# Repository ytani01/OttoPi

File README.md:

# OttoPi: Otto DIY like biped robot for Raspberry Pi

see [github pages](https://ytani01.github.io/OttoPi/)

## Power ON/OFF Button

### Power ON button

GPIO 3 -> SW -> GND

### Shutdown button

GPIO 4 -> SW -> GND
GPIO 21 -> R(1K ohm) -> LED -> GND

```
dtoverlay=gpio-shutdown,gpio_pin=4
dtoverlay=gpio-poweroff,gpiopin=21,active_low=1
```

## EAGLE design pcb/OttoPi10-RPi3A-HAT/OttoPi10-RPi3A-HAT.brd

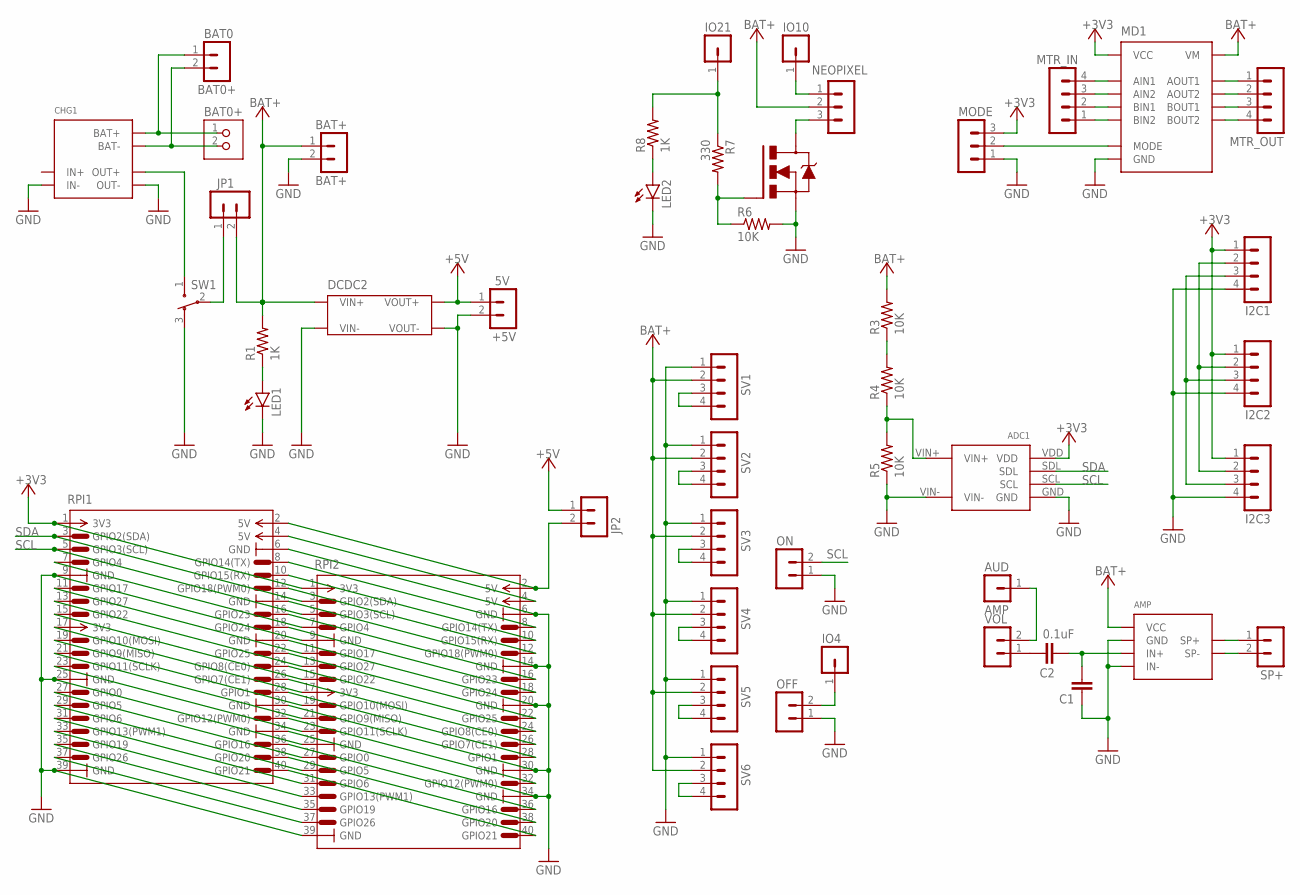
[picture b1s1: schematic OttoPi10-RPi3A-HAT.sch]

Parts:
+5V: 5V; PINHEAD-MA02-1
ADC1: MCP3425MOD
AMP: AMP; PAM8012MOD-A
AUD: AMP; PINHEAD-MA01-1
BAT0: BAT0+; PINHEAD-MA02-1
BAT0+: JST-PH2
BAT+: BAT+; PINHEAD-MA02-1
C1: C-EU025-024X044; C025-024X044
C2: 0.1uF; C025-024X044
CHG1: TP4056MOD1
DCDC2: DCDC-SX1308-MOD1
I2C1, I2C2, I2C3: PINHEAD-MA04-1
IO4, IO10, IO21: PINHEAD-MA01-1
JP1, JP2: PINHEAD-MA02-1
LED1, LED2: LED3MM
MD1: DRV8835MOD
MODE: PINHEAD-MA03-1
MTR_IN: PINHEAD-MA04-1
MTR_OUT: PINHEAD-MA04-1
NEOPIXEL: PINHEAD-MA03-1
OFF: PINHEAD-MA02-1
ON: PINHEAD-MA02-1
Q1: 2SK4017; MOSFET-1
R1, R8: 1K; 0204/7
R3, R4, R5, R6: 10K; 0204/7
R7: 330; 0204/7
RPI1, RPI2: RPI-PIN
SP+: PINHEAD-MA02-1
SV1, SV2, SV3, SV4, SV5, SV6: PINHEAD-MA04-1
SW1: SW3-1
VOL: PINHEAD-MA02-1

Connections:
+3V3: ADC1.VDD, I2C1.1, I2C2.1, I2C3.1, MD1.VCC, MODE.3, RPI1.1 (3V3), RPI2.1 (3V3)
+5V: +5V.1, DCDC2.VOUT+, JP2.1
AIN1: MD1.AIN1, MTR_IN.4
AIN2: MD1.AIN2, MTR_IN.3
AOUT1: MD1.AOUT1, MTR_OUT.1
AOUT2: MD1.AOUT2, MTR_OUT.2
AUDIO0: AUD.1, VOL.2
AUDIO1: AMP.IN+, C1.2, C2.1
BAT+: AMP.V+ (VCC), BAT+.1, DCDC2.VIN+, JP1.2, MD1.VM, NEOPIXEL.2, R1.2, R3.2, SV1.2, SV2.2, SV3.2, SV4.2, SV5.2, SV6.2
BAT+0: BAT0.1, BAT0+.1, CHG1.BAT+
BAT+1: CHG1.OUT+, SW1.1
BAT+2: JP1.1, SW1.2
BAT-0: BAT0.2, BAT0+.2, CHG1.BAT-
BIN1: MD1.BIN1, MTR_IN.2
BIN2: MD1.BIN2, MTR_IN.1
BOUT1: MD1.BOUT1, MTR_OUT.3
BOUT2: MD1.BOUT2, MTR_OUT.4
GND: +5V.2, ADC1.GND, ADC1.VIN-, AMP.GND, AMP.IN-, BAT+.2, C1.1, CHG1.IN-, CHG1.OUT-, DCDC2.VIN-, DCDC2.VOUT-, I2C1.4, I2C2.4, I2C3.4, LED1.K (C), LED2.K (C), MD1.GND, MODE.1, OFF.1, ON.1, Q1.S, R5.1, R6.2, RPI1.6 (GND), RPI1.9 (GND), RPI1.14 (GND), RPI1.20 (GND), RPI1.25 (GND), RPI1.30 (GND), RPI1.34 (GND), RPI1.39 (GND), RPI2.6 (GND), RPI2.9 (GND), RPI2.14 (GND), RPI2.20 (GND), RPI2.25 (GND), RPI2.30 (GND), RPI2.34 (GND), RPI2.39 (GND), SV1.1, SV2.1, SV3.1, SV4.1, SV5.1, SV6.1, SW1.3
GPIO10: RPI1.17 (3V3), RPI2.17 (3V3)
MODE: MD1.MODE, MODE.2
unnamed: Q1.G, R6.1, R7.2
unnamed: NEOPIXEL.3, Q1.D
unnamed: LED1.A, R1.1
unnamed: IO21.1, R7.1, R8.2
unnamed: JP2.2, RPI1.2 (5V), RPI2.2 (5V)
unnamed: RPI1.7 (GPIO4), RPI2.7 (GPIO4)
unnamed: IO10.1, NEOPIXEL.1
unnamed: RPI1.11 (GPIO17), RPI2.11 (GPIO17)
unnamed: RPI1.13 (GPIO27), RPI2.13 (GPIO27)
unnamed: RPI1.15 (GPIO22), RPI2.15 (GPIO22)
unnamed: RPI1.23 (GPIO11(SCLK)), RPI2.23 (GPIO11(SCLK))
unnamed: RPI1.19 (GPIO10(MOSI)), RPI2.19 (GPIO10(MOSI))
unnamed: RPI1.21 (GPIO9(MISO)), RPI2.21 (GPIO9(MISO))
unnamed: C2.2, VOL.1
unnamed: RPI1.4 (5V), RPI2.4 (5V)
unnamed: LED2.A, R8.1
unnamed: RPI1.8 (GPIO14(TX)), RPI2.8 (GPIO14(TX))
unnamed: RPI1.10 (GPIO15(RX)), RPI2.10 (GPIO15(RX))
unnamed: RPI1.12 (GPIO18(PWM0)), RPI2.12 (GPIO18(PWM0))
unnamed: RPI1.16 (GPIO23), RPI2.16 (GPIO23)
unnamed: RPI1.18 (GPIO24), RPI2.18 (GPIO24)
unnamed: RPI1.22 (GPIO25), RPI2.22 (GPIO25)
unnamed: IO4.1, OFF.2
unnamed: R3.1, R4.2
unnamed: ADC1.VIN+, R4.1, R5.2
unnamed: RPI1.24 (GPIO8(CE0)), RPI2.24 (GPIO8(CE0))
unnamed: RPI1.26 (GPIO7(CE1)), RPI2.26 (GPIO7(CE1))
unnamed: RPI1.27 (GPIO0), RPI2.27 (GPIO0)
unnamed: RPI1.28 (GPIO1), RPI2.28 (GPIO1)
unnamed: RPI1.29 (GPIO5), RPI2.29 (GPIO5)
unnamed: RPI1.31 (GPIO6), RPI2.31 (GPIO6)
unnamed: RPI1.32 (GPIO12(PWM0)), RPI2.32 (GPIO12(PWM0))
unnamed: RPI1.33 (GPIO13(PWM1)), RPI2.33 (GPIO13(PWM1))
unnamed: RPI1.35 (GPIO19), RPI2.35 (GPIO19)
unnamed: RPI1.36 (GPIO16), RPI2.36 (GPIO16)
unnamed: RPI1.37 (GPIO26), RPI2.37 (GPIO26)
unnamed: RPI1.38 (GPIO20), RPI2.38 (GPIO20)
unnamed: RPI1.40 (GPIO21), RPI2.40 (GPIO21)
unnamed: SV2.3, SV2.4
unnamed: SV3.3, SV3.4
unnamed: SV4.3, SV4.4
unnamed: SV1.3, SV1.4
unnamed: SV5.3, SV5.4
unnamed: SV6.3, SV6.4
SCL: ADC1.SCL, I2C1.3, I2C2.3, I2C3.3, ON.2, RPI1.5 (GPIO3(SCL)), RPI2.5 (GPIO3(SCL))
SDA: ADC1.SDL, I2C1.2, I2C2.2, I2C3.2, RPI1.3 (GPIO2(SDA)), RPI2.3 (GPIO2(SDA))
SP+: AMP.SP+@1 (SP+), SP+.1
SP-: AMP.SP-@1 (SP-), SP+.2

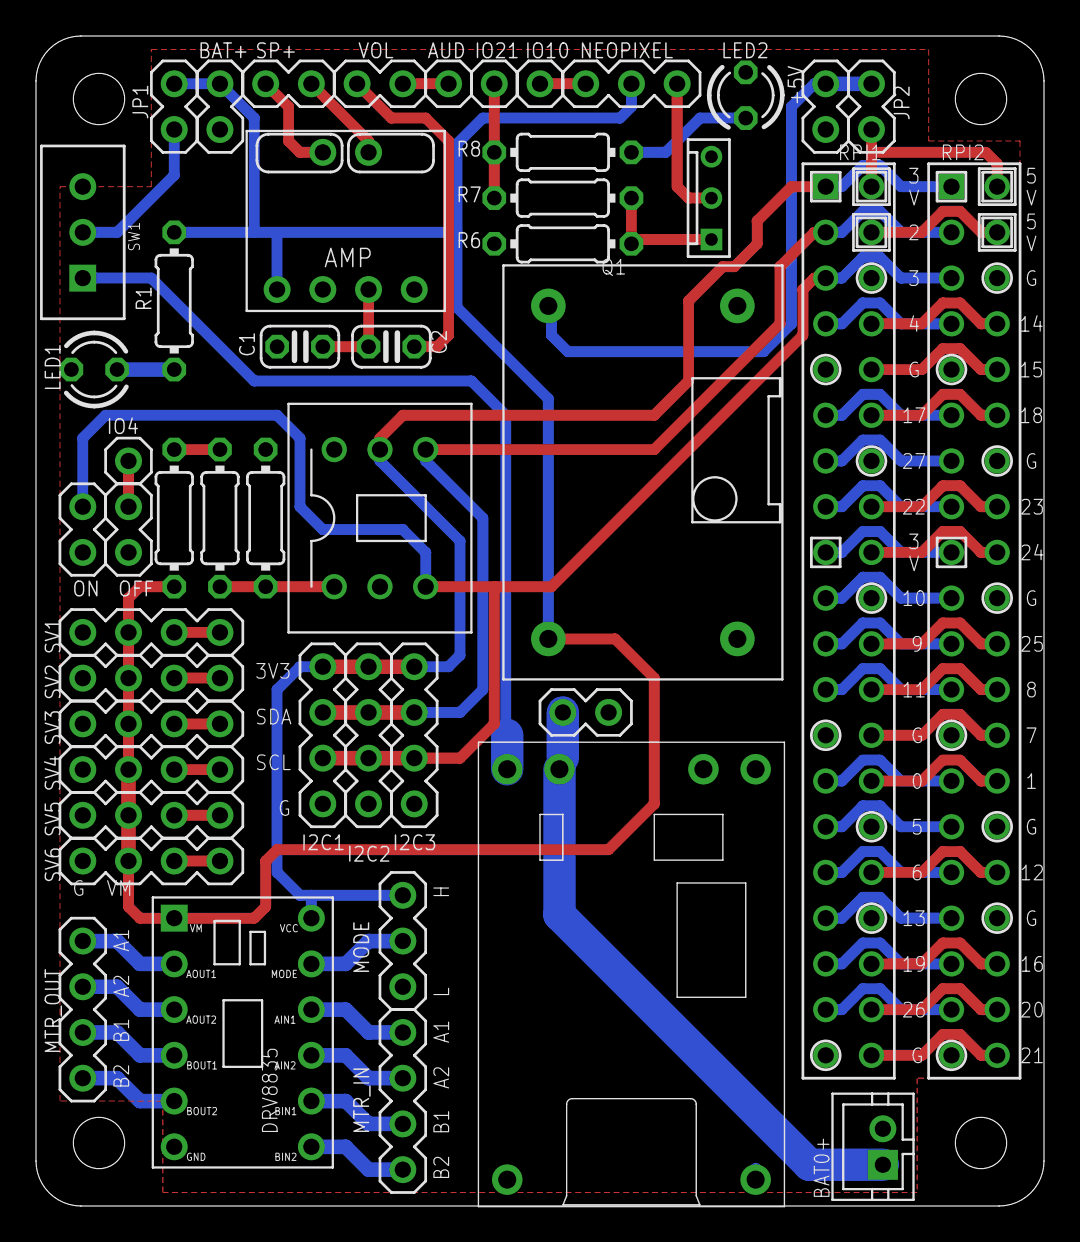
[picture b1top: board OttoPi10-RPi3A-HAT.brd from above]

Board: 2 copper layers, 56.0 x 65.0 mm, 47 parts (0 on the bottom side), 68 nets.

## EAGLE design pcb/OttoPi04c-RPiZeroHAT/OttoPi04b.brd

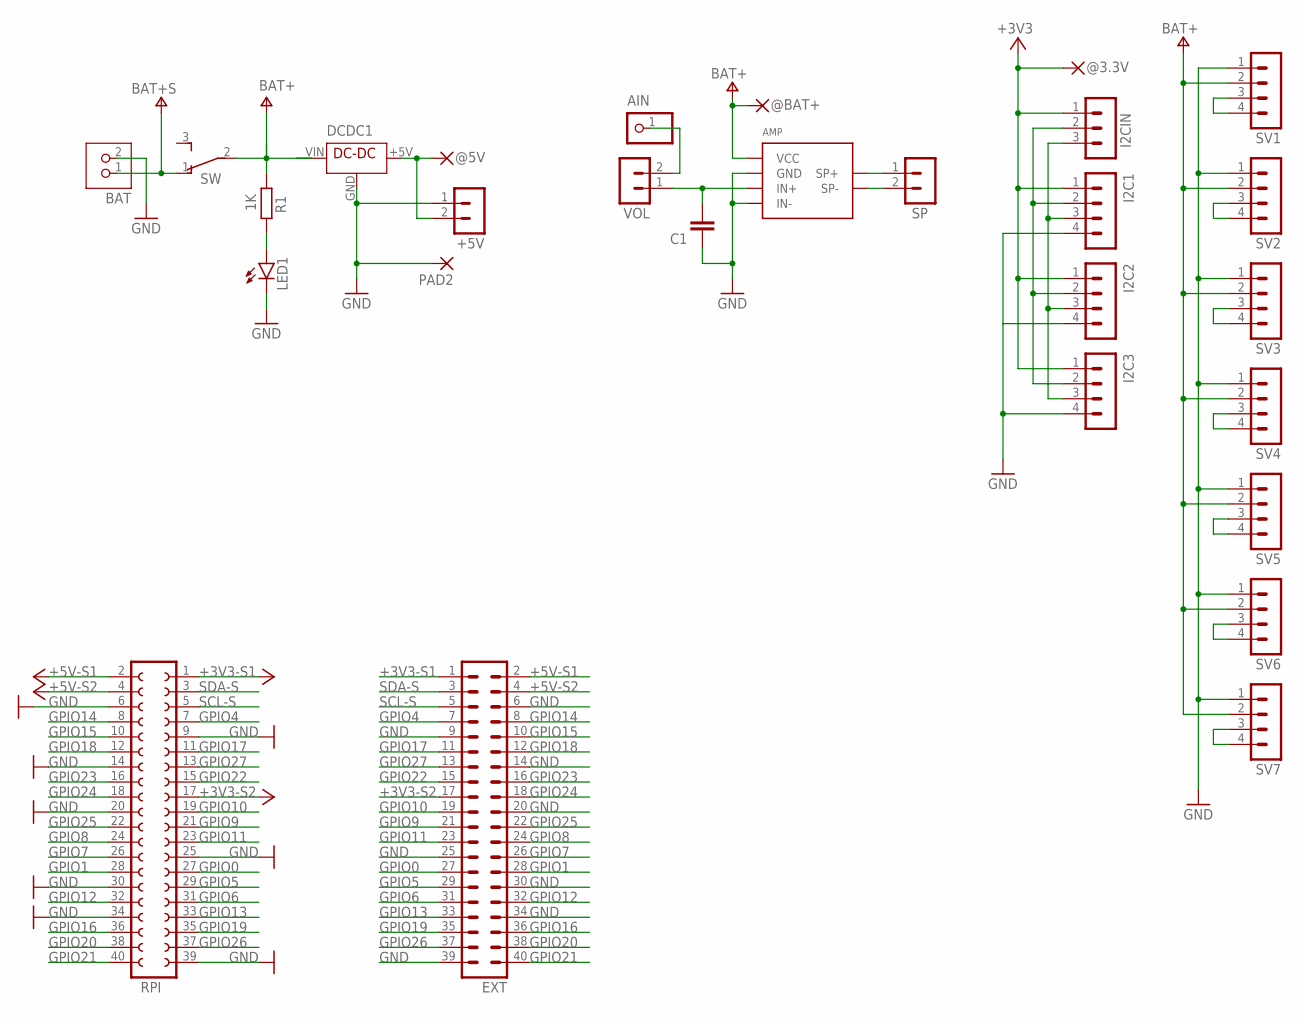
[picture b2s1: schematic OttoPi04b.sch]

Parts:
+5V: MA02-1
@3.3V, @5V: 1,6/0,9
@BAT+: 1,6/0,9
AIN: PINHD-1X1; 1X01
AMP: PAM8012MOD; PAM8012MOD-A
BAT: JST-PH2
C1: C-EU025-024X044; C025-024X044
DCDC1: DCDC-5V-0.48A
EXT: MA20-2
I2C1, I2C2, I2C3: MA04-1
I2CIN: MA03-1
LED1: LED3MM
PAD2: 1,6/0,9
R1: 1K; 0204/7
RPI: FE20-2
SP: MA02-1
SV1, SV2, SV3, SV4, SV5, SV6, SV7: MA04-1
SW: TL36PO; TL3XPO
VOL: MA02-1

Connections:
+3V3: @3.3V.1, I2C1.1, I2C2.1, I2C3.1, I2CIN.1
+3V3-S1: EXT.1, RPI.1
+3V3-S2: EXT.17, RPI.17
+4V_S: BAT.1, SW.1 (O)
+5V: +5V.2, @5V.1, DCDC1.+5V (VOUT)
+5V-S1: EXT.2, RPI.2
+5V-S2: EXT.4, RPI.4
AIN: AMP.IN+, C1.1, VOL.1
GND: +5V.1, AMP.GND, AMP.IN-, BAT.2, C1.2, DCDC1.GND, EXT.6, EXT.9, EXT.14, EXT.20, EXT.25, EXT.30, EXT.34, EXT.39, I2C1.4, I2C2.4, I2C3.4, LED1.K (C), PAD2.1, RPI.6, RPI.9, RPI.14, RPI.20, RPI.25, RPI.30, RPI.34, RPI.39, SV1.1, SV2.1, SV3.1, SV4.1, SV5.1, SV6.1, SV7.1
GPIO0: EXT.27, RPI.27
GPIO1: EXT.28, RPI.28
GPIO4: EXT.7, RPI.7
GPIO5: EXT.29, RPI.29
GPIO6: EXT.31, RPI.31
GPIO7: EXT.26, RPI.26
GPIO8: EXT.24, RPI.24
GPIO9: EXT.21, RPI.21
GPIO10: EXT.19, RPI.19
GPIO11: EXT.23, RPI.23
GPIO12: EXT.32, RPI.32
GPIO13: EXT.33, RPI.33
GPIO14: EXT.8, RPI.8
GPIO15: EXT.10, RPI.10
GPIO16: EXT.36, RPI.36
GPIO17: EXT.11, RPI.11
GPIO18: EXT.12, RPI.12
GPIO19: EXT.35, RPI.35
GPIO20: EXT.38, RPI.38
GPIO21: EXT.40, RPI.40
GPIO22: EXT.15, RPI.15
GPIO23: EXT.16, RPI.16
GPIO24: EXT.18, RPI.18
GPIO25: EXT.22, RPI.22
GPIO26: EXT.37, RPI.37
GPIO27: EXT.13, RPI.13
LED: LED1.A, R1.1
unnamed: AIN.1, VOL.2
unnamed: SV6.3, SV6.4
unnamed: SV7.3, SV7.4
SCL: I2C1.3, I2C2.3, I2C3.3, I2CIN.3
SCL-S: EXT.5, RPI.5
SDA-S: EXT.3, RPI.3
SDL: I2C1.2, I2C2.2, I2C3.2, I2CIN.2
SP+: AMP.SP+@1 (SP+), SP.1
SP-: AMP.SP-@1 (SP-), SP.2
SV1: SV5.3, SV5.4
SV2: SV4.3, SV4.4
SV3: SV3.3, SV3.4
SV4: SV2.3, SV2.4
SV5: SV1.3, SV1.4
V+: @BAT+.1, AMP.V+ (VCC), DCDC1.VIN, R1.2, SV1.2, SV2.2, SV3.2, SV4.2, SV5.2, SV6.2, SV7.2, SW.2

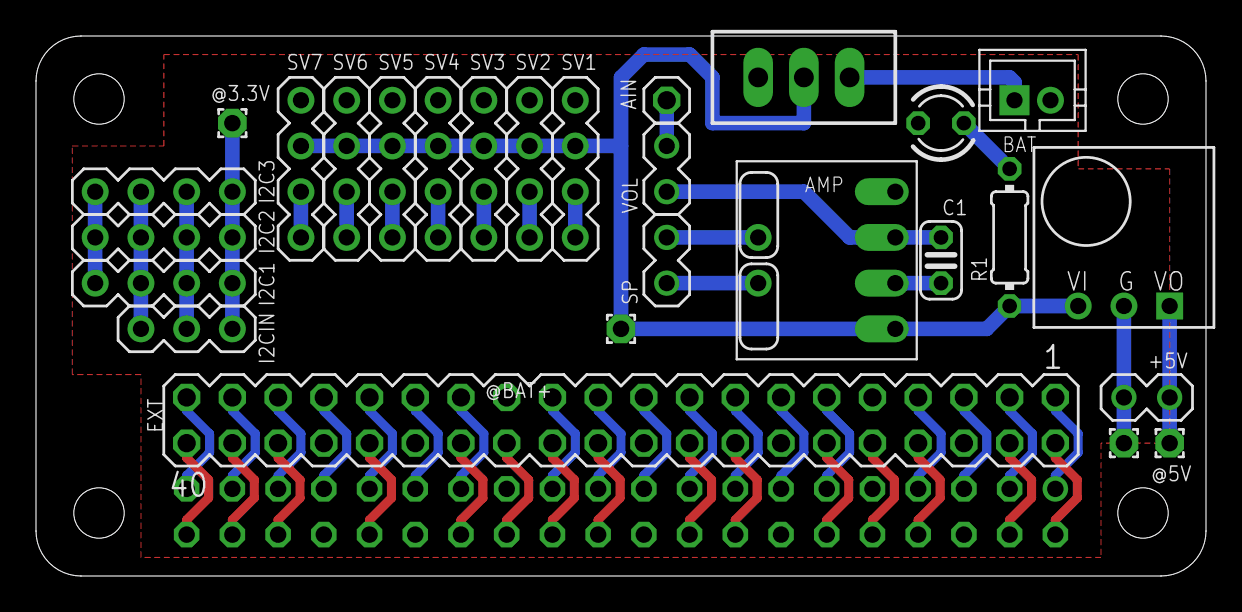
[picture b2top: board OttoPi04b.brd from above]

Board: 2 copper layers, 65.0 x 30.0 mm, 28 parts (1 on the bottom side), 51 nets.

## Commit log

2019-05-07 OttoPi.py
2019-05-09 OttoPiCtrl.py
2019-05-10 side*()
2019-05-11 OttoPiServer.py
2019-05-11 README.md
2019-05-12 pipenv
2019-05-14 HTTP Server
2019-09-25 OttoPi-01.fzz
2019-11-08 init.el
2019-11-11 sound
2020-01-06 Set theme jekyll-theme-cayman
2020-03-07 websockets
2020-03-20 BleServer
2020-03-25 bug fix
2020-03-30 Set theme jekyll-theme-leap-day
2020-04-05 ble_observer.ino
2020-09-04 update pcb
2020-09-09 pcb/OttoPi04
2020-09-14 pcb/OttoPi04-RPiZeroHAT
2020-10-13 docs
2020-10-13 Set theme jekyll-theme-minimal
2020-10-23 OttoPi-Web1.png
2020-11-02 body
2020-11-05 music
2020-12-28 [update] PCB
2021-01-27 Youtube link
2021-06-12 [add] media/
2021-07-01 UPDATE: SPEECH_INTERVAL=120
2021-09-04 UPD: docs/index.md
2021-09-21 ADD: pcb/OttoPi08-RPi3AHAT
2021-09-22 UPD: pcb/OttoPi08-RPi3AHAT
2021-09-27 ADD: pcb/OttoPi09-RPi3A-HAT
2021-09-30 UPD: pcb
2021-10-01 UPD: README.md
2021-10-03 UPD: music
2021-11-01 UPD: hi_right, hi_left, bye_right, bye_left
2021-11-01 ADD: dance.py
2021-11-02 UPD: Motion
2021-11-02 UPD: OttoPiMotion.py
2021-11-02 UPD: Dance mode
2021-11-04 UPD: OttoPiMotion.py dance.py etc.
2021-11-04 UPD: index.html
2021-11-05 UPD: update
2021-11-05 UPD: dance
2021-11-13 ADD: dance2
2021-11-13 UPD: OttoPiMotion PiServo
2022-06-13 ADD: ScratchLink/
2022-06-13 ADD: junk file
2022-06-13 DEL: junk
2023-02-20 ADD: pcb/OttoPi10-
2023-05-31 zero01
2023-06-01 PiServo.py
2025-03-08 ADD: pcb/.../KiCAD/
2025-11-12 ADD: pcb/OttoPi10-Rpi3A-HAT/..
